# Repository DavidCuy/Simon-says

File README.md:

# Simon-says
An arduino-based popular game simon says.

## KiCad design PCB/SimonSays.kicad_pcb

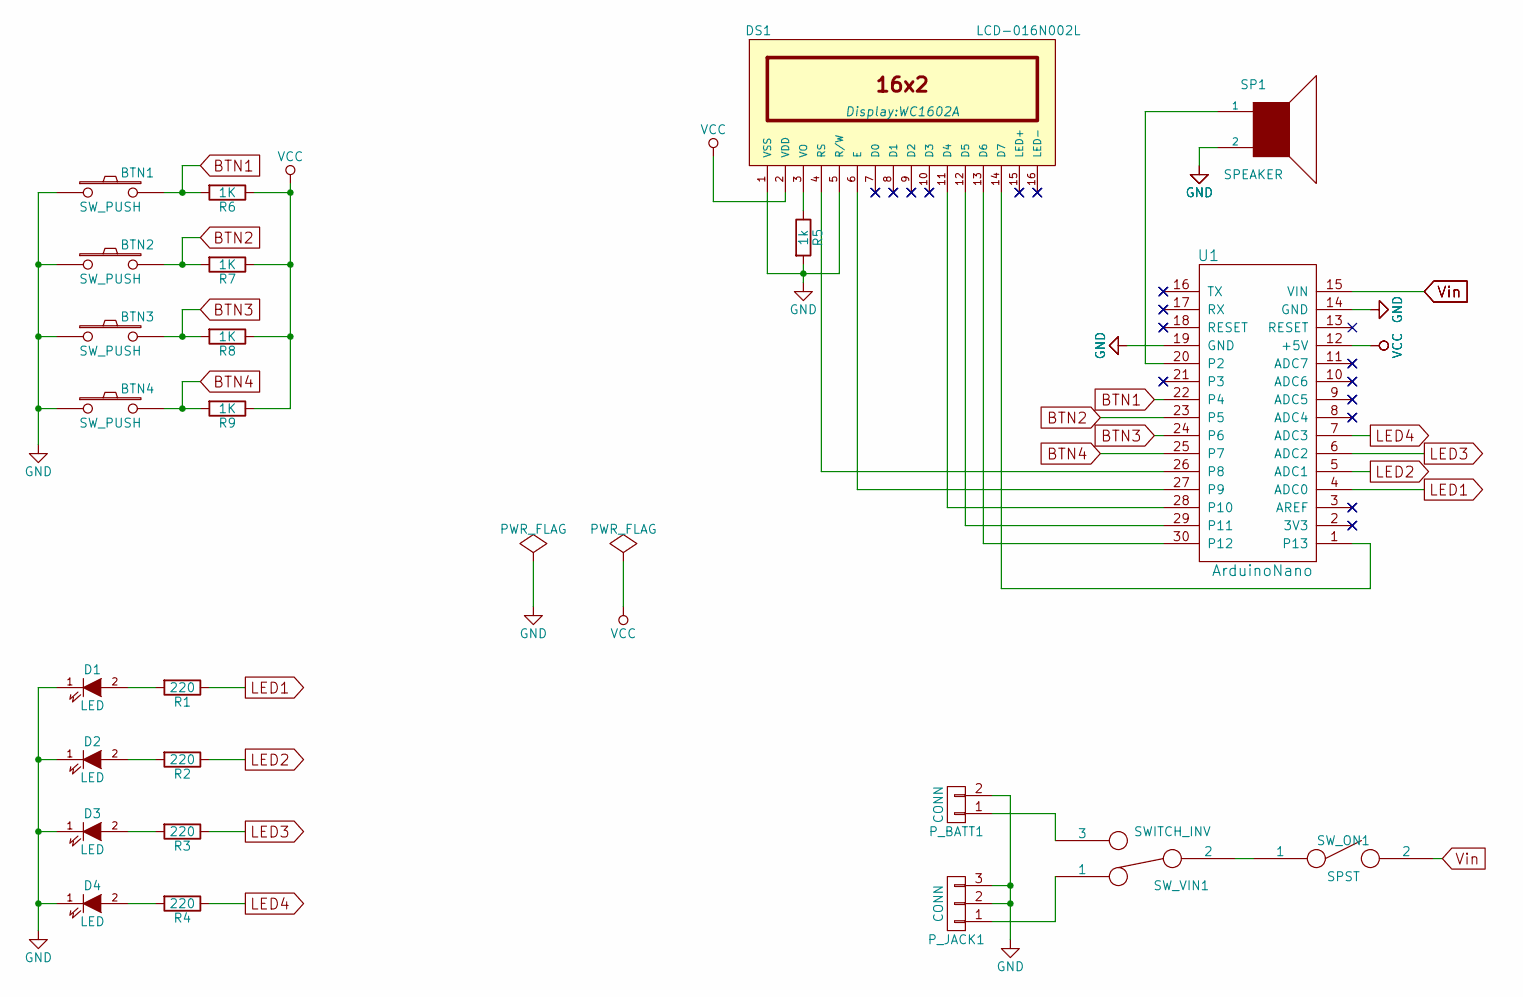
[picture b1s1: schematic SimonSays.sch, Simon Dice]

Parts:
BTN1, BTN2, BTN3, BTN4: SW_PUSH; SW_PUSH-12mm
D1, D2, D3, D4: LED; LED_D5.0mm
DS1: LCD-016N002L; WC1602A
P_BATT1: CONN; mors_2p
P_JACK1: CONN; dc_socket
R1, R2, R3, R4: 220; RC05
R5: 1k; RC05
R6, R7, R8, R9: 1K; RC05
SP1: SPEAKER; BUZZER
SW_ON1: SPST; dip_1-300
SW_VIN1: SWITCH_INV; switch_mfp116dg-ra
U1: ArduinoNano; arduino_nano_header

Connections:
BTN1: BTN1.2, R6.2, U1.22 (P4)
BTN2: BTN2.2, R7.2, U1.23 (P5)
BTN3: BTN3.2, R8.2, U1.24 (P6)
BTN4: BTN4.2, R9.2, U1.25 (P7)
GND: BTN1.1, BTN2.1, BTN3.1, BTN4.1, D1.1 (K), D2.1 (K), D3.1 (K), D4.1 (K), DS1.1 (VSS), DS1.5 (R/W), P_BATT1.2, P_JACK1.2, P_JACK1.3, R5.2, SP1.2, U1.14 (GND), U1.19 (GND)
LED1: R1.1, U1.4 (ADC0)
LED2: R2.1, U1.5 (ADC1)
LED3: R3.1, U1.6 (ADC2)
LED4: R4.1, U1.7 (ADC3)
unnamed: D1.2 (A), R1.2
unnamed: D2.2 (A), R2.2
unnamed: D3.2 (A), R3.2
unnamed: D4.2 (A), R4.2
unnamed: DS1.3 (VO), R5.1
unnamed: DS1.4 (RS), U1.26 (P8)
unnamed: DS1.6 (E), U1.27 (P9)
unnamed: DS1.11 (D4), U1.28 (P10)
unnamed: DS1.12 (D5), U1.29 (P11)
unnamed: DS1.13 (D6), U1.30 (P12)
unnamed: DS1.14 (D7), U1.1 (P13)
unnamed: P_BATT1.1, SW_VIN1.3
unnamed: P_JACK1.1, SW_VIN1.1
unnamed: SP1.1, U1.20 (P2)
unnamed: SW_ON1.1, SW_VIN1.2
VCC: DS1.2 (VDD), R6.1, R7.1, R8.1, R9.1, U1.12 (+5V)
Vin: SW_ON1.2, U1.15 (VIN)

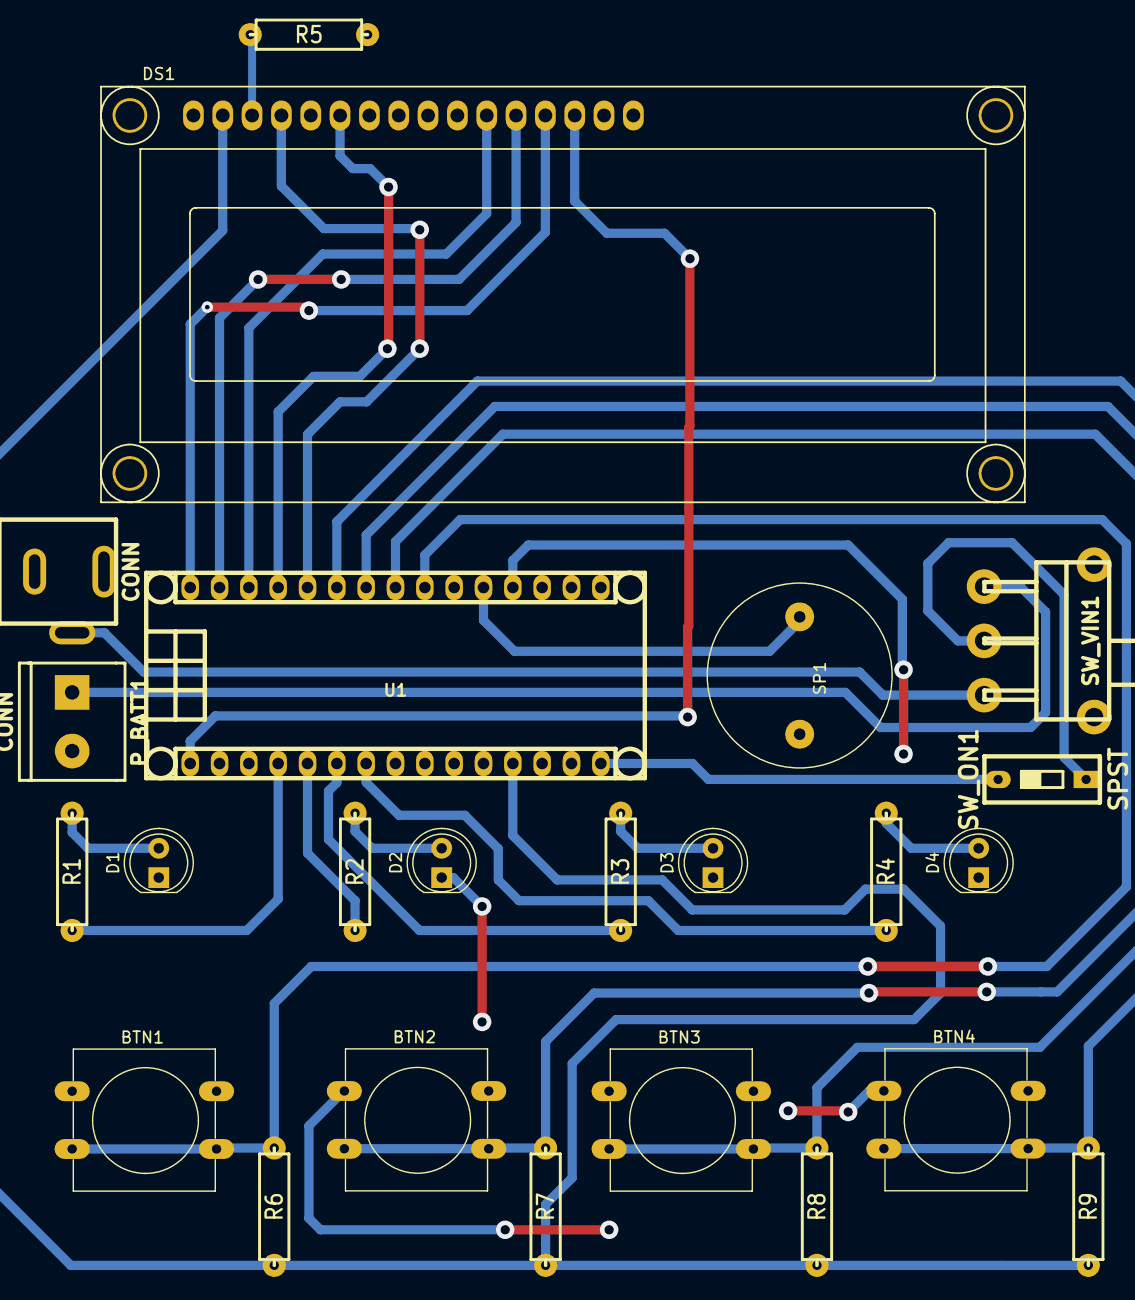
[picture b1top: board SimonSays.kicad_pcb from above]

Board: 2 copper layers, 24 parts (0 on the bottom side), 26 nets.

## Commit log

2017-10-02 Arduino code
    The code runs in arduino, uses 4 leds, 4 buttons, a LCD and an arduino
    mini
2017-10-02 Prototype example
    This is for didactic use.
2017-10-02 Cambio en la posicion de los pines de LEDs
2017-10-02 PCB y esquematicos
